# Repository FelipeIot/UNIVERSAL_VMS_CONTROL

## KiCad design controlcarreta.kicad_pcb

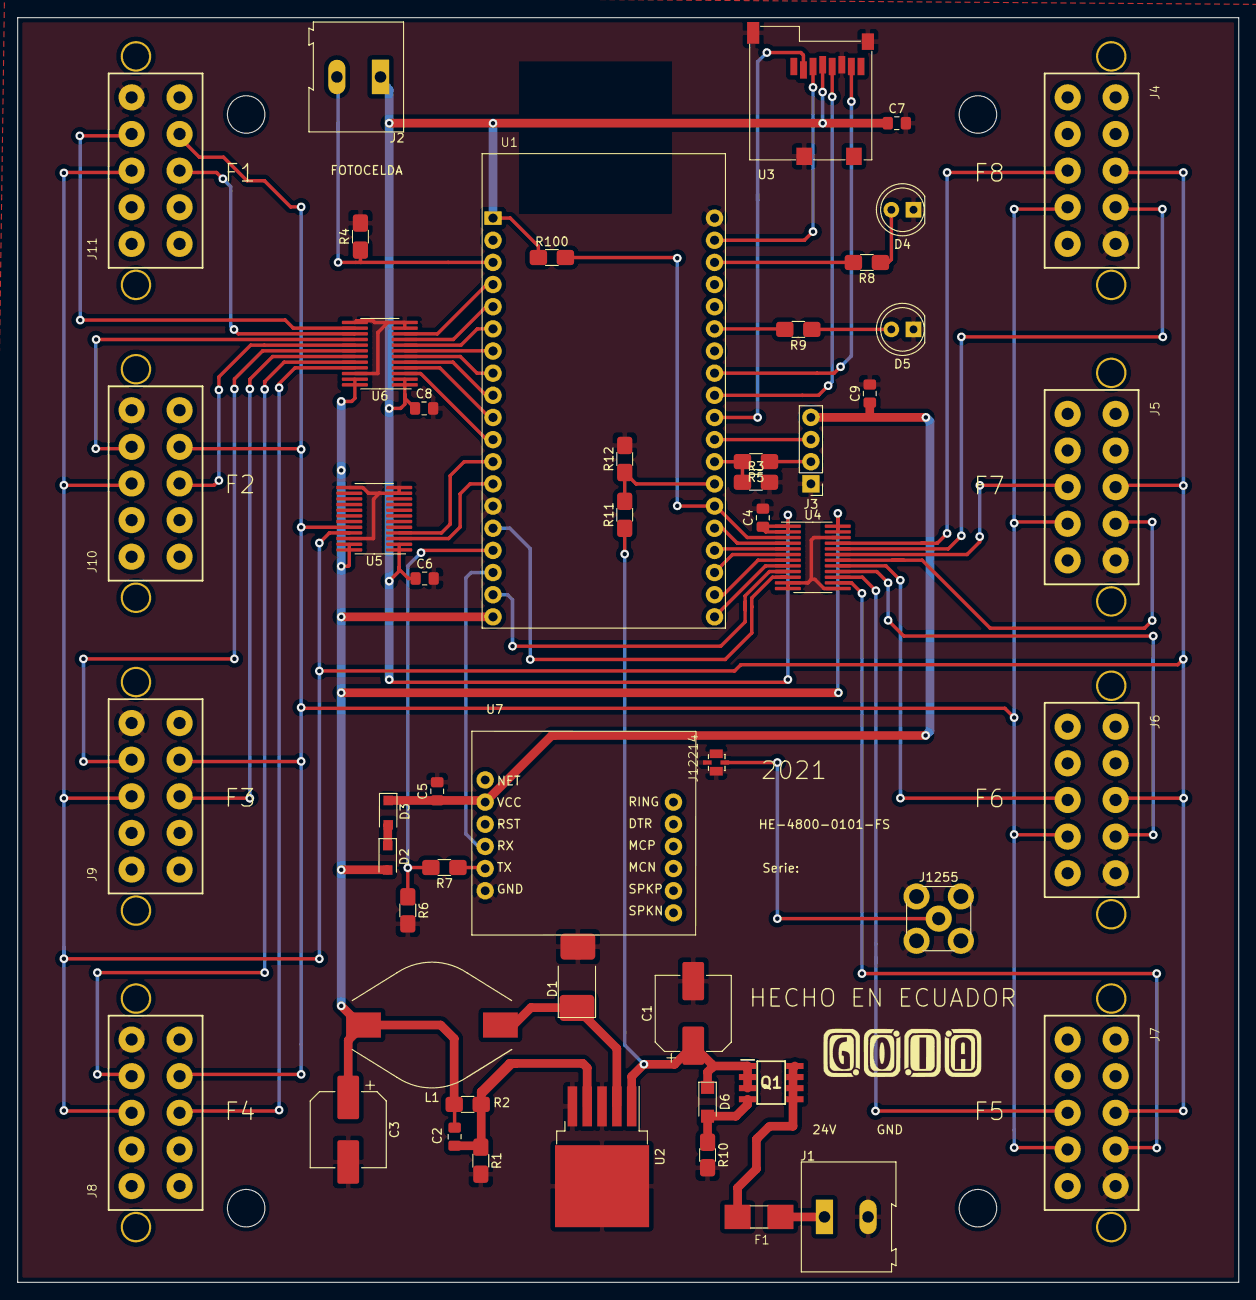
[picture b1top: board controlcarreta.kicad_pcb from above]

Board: 2 copper layers, 140.0 x 145.0 mm, 55 parts (0 on the bottom side), 64 nets.

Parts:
C1, C3: CP; CP_Elec_8x10.5
C2: CAP; C_0805_2012Metric_Pad1.18x1.45mm_HandSolder
C4, C5, C6, C7, C8, C9: C; C_0805_2012Metric_Pad1.18x1.45mm_HandSolder
D1: D_Zener; D_2114_3652Metric
D2, D3: 1N4007; D_SOD-123F
D4, D5: LED; LED_D5.0mm
D6: D_Zener; D_SOD-123
F1: 0679L5000-05; FUSC6125X279N
H1, H2, H3, H4: MountingHole; MountingHole_4.3mm_M4
J1, J2: Screw_Terminal_01x02; TerminalBlock_Altech_AK300-2_P5.00mm
J3: Conn_01x04_Male; PinHeader_1x04_P2.54mm_Vertical
J4, J5, J6, J7, J8, J9, J10, J11: MOLEX10POS
J1255: Conn_Coaxial; SMA_Amphenol_132134-16_Vertical
J12214: RSP-122811-02; SAMTEC_RSP-122811-02
L1: INDUCTOR; L_Bourns_SDR1806
Q1: SI4447ADY-T1-GE3; SOIC127P600X175-8N
R1, R12: 1k; R_1206_3216Metric_Pad1.30x1.75mm_HandSolder
R2: 3k; R_1206_3216Metric_Pad1.30x1.75mm_HandSolder
R3, R4, R6: 10k; R_1206_3216Metric_Pad1.30x1.75mm_HandSolder
R5, R7: 1.5k; R_1206_3216Metric_Pad1.30x1.75mm_HandSolder
R8, R9: 330 ohm; R_1206_3216Metric_Pad1.30x1.75mm_HandSolder
R10: 100K; R_1206_3216Metric
R11: 22k; R_1206_3216Metric_Pad1.30x1.75mm_HandSolder
R100: R; R_1206_3216Metric_Pad1.30x1.75mm_HandSolder
U1: ESP32-DEVKITC-32D; MODULE_ESP32-DEVKITC-32D
U2: LM2596S-ADJ; TO-263-5_TabPin3
U3: sdcard; sdcardgoia
U4, U5, U6: 74LVC8T245PW; TSSOP-24_4.4x7.8mm_P0.65mm
U7: sim800l

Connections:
+3V3: C4.1, C6.1, C7.1, C8.1, J2.1, R100.1, U1.1, U3.4, U4.1, U4.2, U5.1, U5.2, U6.1, U6.2
+3V8: C5.1, C9.1, D3.1, J3.4, U7.2
+5V: C2.1, C3.1, D2.2, L1.2, R2.1, U1.19, U4.23, U4.24, U5.23, U5.24, U6.23, U6.24
+24V: C1.1, D6.1, Q1.1, Q1.2, Q1.3, R11.1, U2.1
/BRILLO: U1.13, U5.3
/CL: U1.12, U5.4
/CLOCK: J4.03, J5.03, J6.03, J7.03, J8.03, J9.03, J10.03, J11.03, U5.20
/D1: U1.34, U4.4
/D2: U1.36, U4.6
/D3: U1.38, U4.8
/D4: U1.15, U4.10
/D5: U1.10, U6.4
/D6: U1.8, U6.6
/D7: U1.6, U6.8
/D8: U1.4, U6.10
/DIM: J4.06, J5.06, J6.06, J7.06, J8.06, J9.06, J10.06, J11.06, U5.21
/FOTO: J2.2, R4.1, U1.3
/LE1: R100.2, U1.33, U4.3
/LE2: U1.35, U4.5
/LE3: U1.37, U4.7
/LE4: U1.18, U4.9
/LE5: U1.11, U6.3
/LE6: U1.9, U6.5
/LE7: U1.7, U6.7
/LE8: U1.5, U6.9
/LEN1: J4.05, U4.21
/LEN2: J5.05, U4.19
/LEN3: J6.05, U4.17
/LEN4: J7.05, U4.15
/LEN5: J8.05, U6.21
/LEN6: J9.05, U6.19
/LEN7: J10.05, U6.17
/LEN8: J11.05, U6.15
/MISO: U1.27, U3.7
/MOSI: U1.21, U3.3
/RX_GPS: J3.3, U1.30
/RX_SIM: U1.17, U7.4
/SCK: U1.28, U3.5
/SIN1: J4.04, U4.20
/SIN2: J5.04, U4.18
/SIN3: J6.04, U4.16
/SIN4: J7.04, U4.14
/SIN5: J8.04, U6.20
/SIN6: J9.04, U6.18
/SIN7: J10.04, U6.16
/SIN8: J11.04, U6.14
/SS: U1.29, U3.2
/TX_GPS: R3.1, R5.2, U1.31
/TX_SIM: R6.1, R7.2, U1.16
/VREAD: R11.2, R12.1, U1.32
GND: C1.2, C3.2, C4.2, C5.2, C6.2, C7.2, C8.2, C9.2, D1.2, D4.1, D5.1, J1.2, J3.1, J4.02, J5.02, J6.02, J7.02, J8.02, J9.02, J10.02, J11.02, J1255.2, J1255.3, J12214.2, J12214.3, J12214.4, R1.2, R3.2, R4.2, R6.2, R10.2, R12.2, U1.14, U1.20, U2.3, U2.5, U3.6, U3.9, U4.11, U4.12, U4.13, U4.22, U5.11, U5.12, U5.13, U5.22, U6.11, U6.12, U6.13, U6.22, U7.6
unnamed: C2.2, R1.1, R2.2, U2.4
unnamed: D1.1, L1.1, U2.2
unnamed: D2.1, D3.2
unnamed: D4.2, R8.1
unnamed: D5.2, R9.1
unnamed: D6.2, Q1.4, R10.1
unnamed: F1.1, J1.1
unnamed: F1.2, Q1.5, Q1.6, Q1.7, Q1.8
unnamed: J3.2, R5.1
unnamed: J1255.1, J12214.1
unnamed: R7.1, U7.5
unnamed: R8.2, U1.22
unnamed: R9.2, U1.25
